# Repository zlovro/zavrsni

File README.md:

## O projektu

Završni rad za kraj školovanja u srednjoj školi (Tehničkoj školi Daruvar).

## Što je ovo?
## Ideja i motivacija
## Odabir sklopova
## Hardverska izvedba
## Elektronički dizajn
## Elektronička shema
## Softverska izvedba
## Primjer rada
## Troškovi izvedbe projekta

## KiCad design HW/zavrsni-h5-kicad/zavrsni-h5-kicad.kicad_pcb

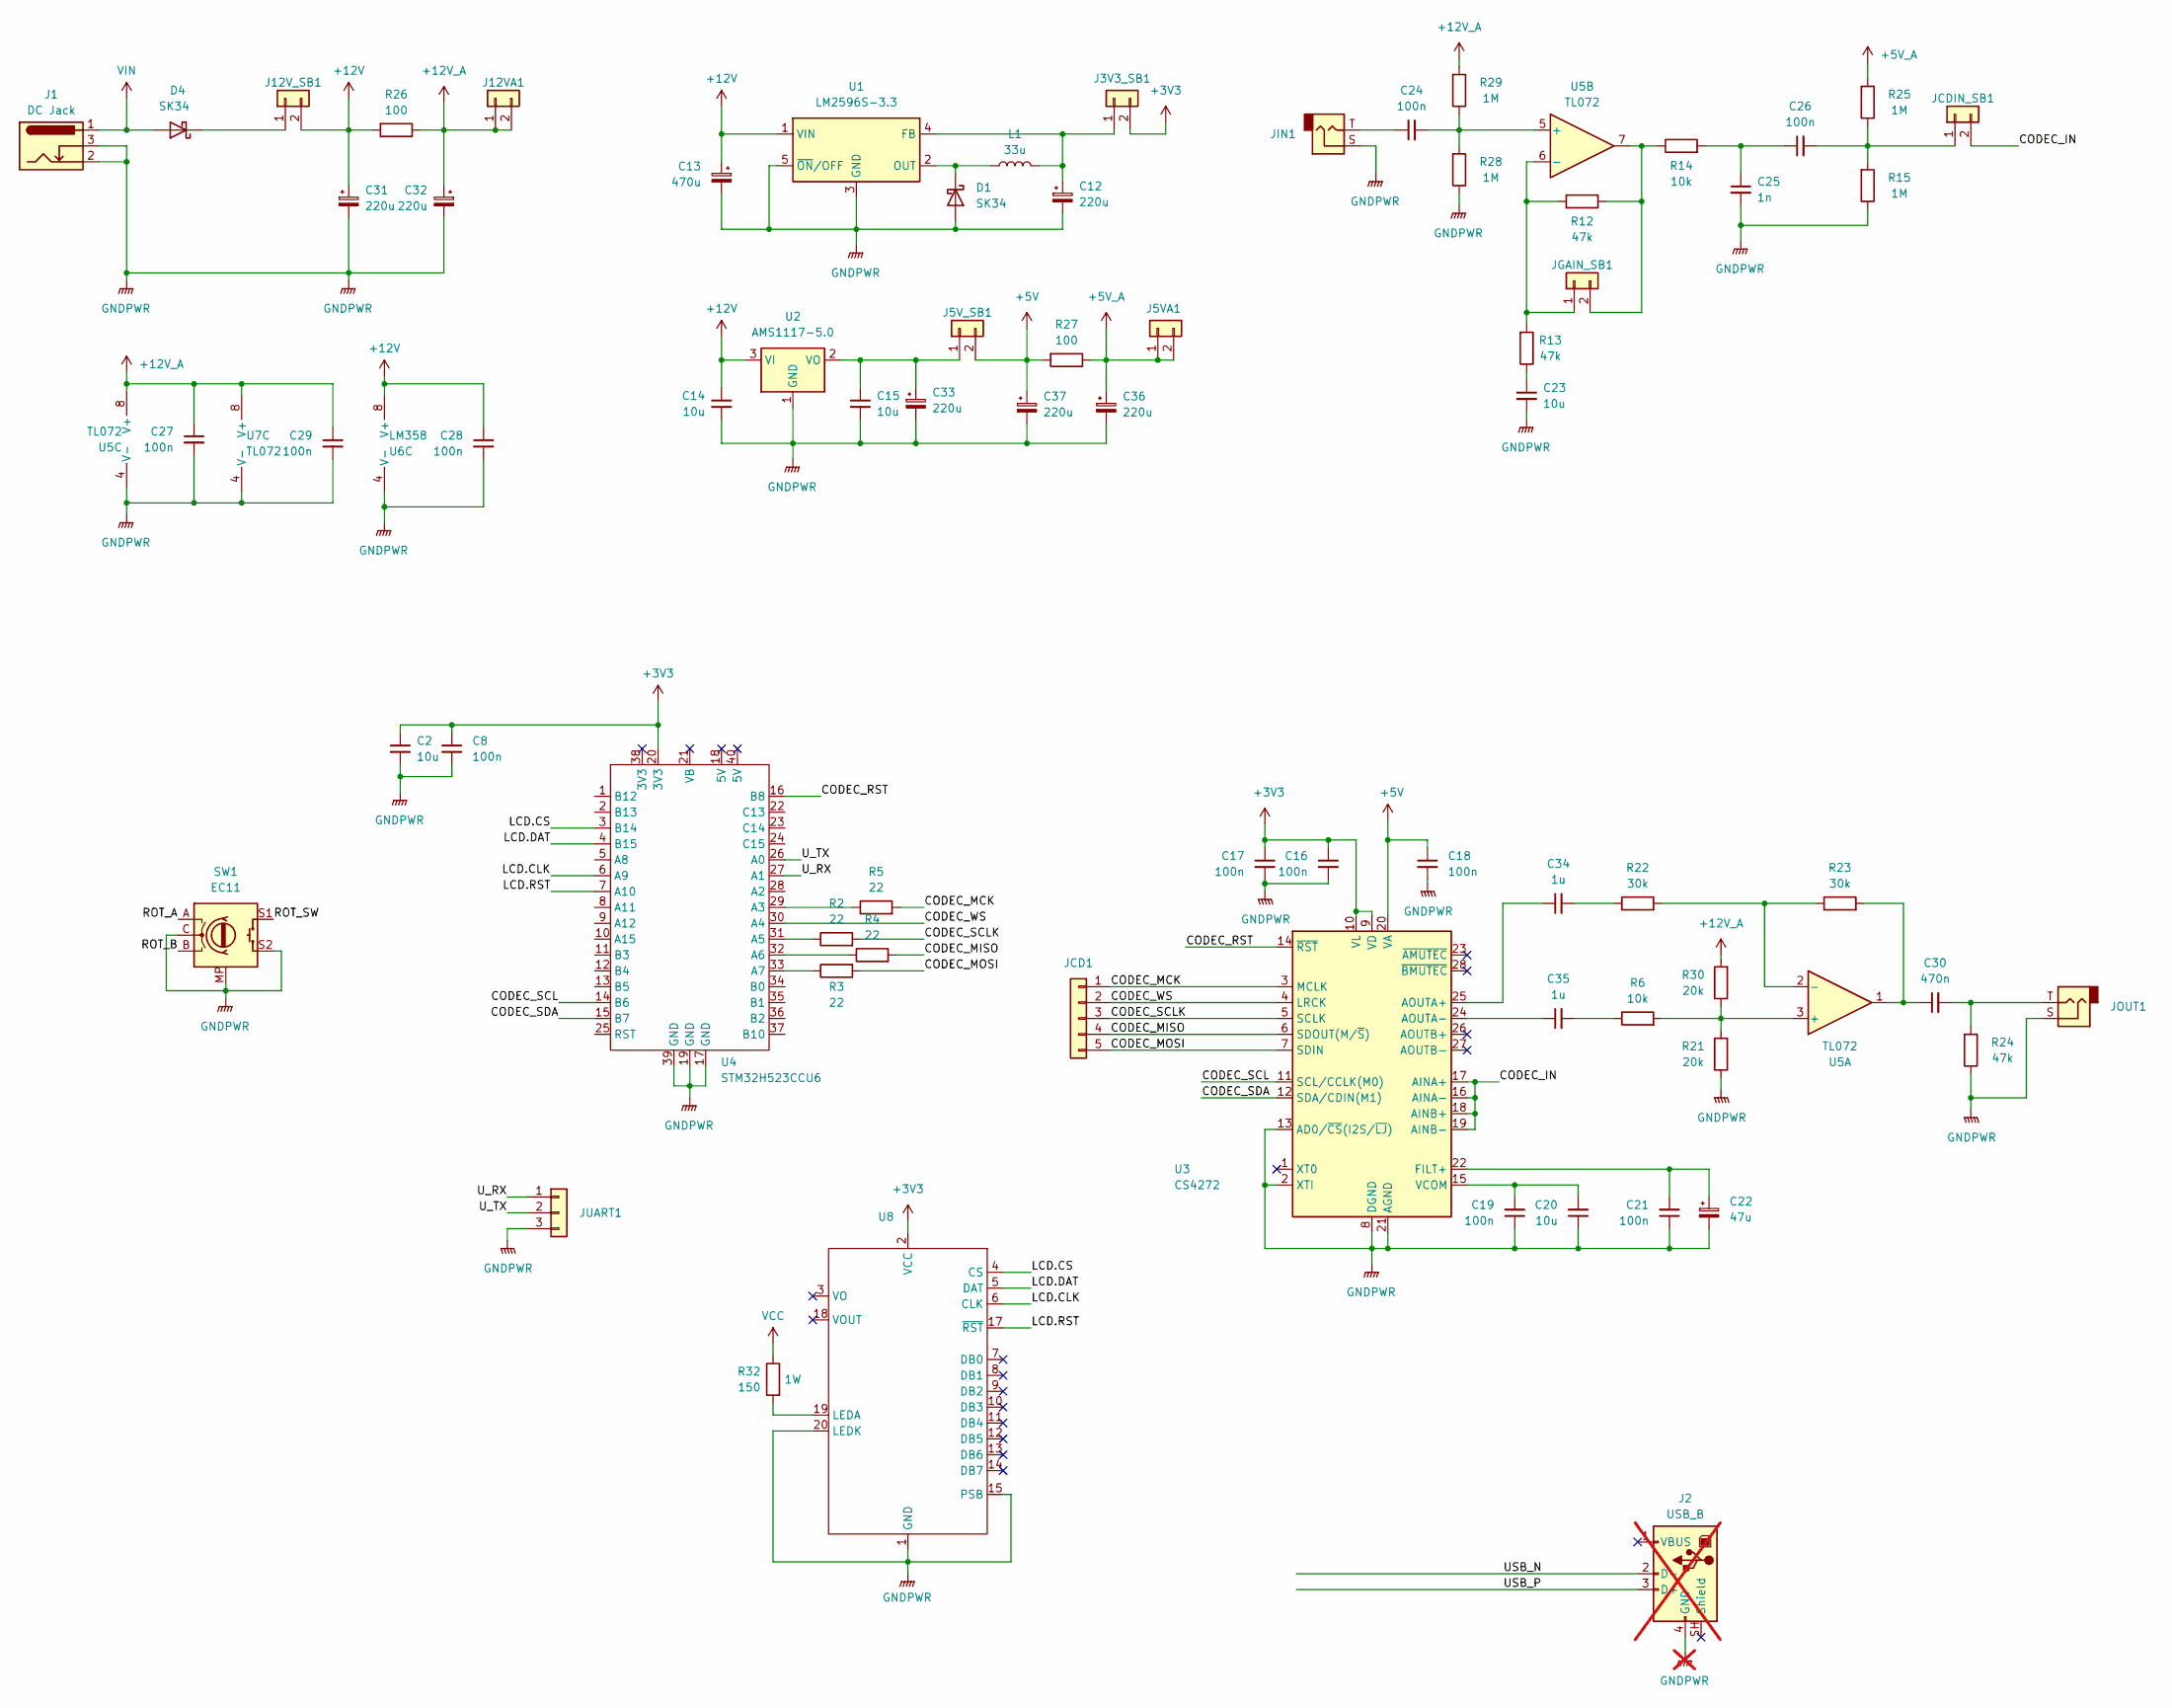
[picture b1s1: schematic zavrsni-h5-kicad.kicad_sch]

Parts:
C2, C14, C15, C20, C23: 10u; C_1206_3216Metric_Pad1.33x1.80mm_HandSolder
C8, C16, C17, C18, C19, C21, C24, C26, C27, C28, C29: 100n; C_1206_3216Metric_Pad1.33x1.80mm_HandSolder
C12, C31, C32, C33, C36, C37: 220u; CP_Radial_D5.0mm_P2.00mm
C13: 470u; CP_Radial_D8.0mm_P3.50mm
C22: 47u; CP_Radial_D4.0mm_P1.50mm
C25: 1n; C_1206_3216Metric_Pad1.33x1.80mm_HandSolder
C30: 470n; C_1206_3216Metric_Pad1.33x1.80mm_HandSolder
C34, C35: 1u; C_1206_3216Metric_Pad1.33x1.80mm_HandSolder
D1, D4: SK34; D_SMB_Handsoldering
J1: DC Jack; BarrelJack_Horizontal
J2: USB_B; USB_B_OST_USB-B1HSxx_Horizontal; not fitted
J3V3_SB1, J5VA1, J5V_SB1, J12VA1, J12V_SB1: Conn_01x02; PinHeader_1x02_P2.54mm_Vertical
JCD1: Conn_01x05; PinHeader_1x05_P2.54mm_Vertical
JCDIN_SB1: Conn_01x02; PinHeader_1x02_P2.54mm_Vertical
JGAIN_SB1: Conn_01x02; SolderJumper-2_P1.3mm_Open_TrianglePad1.0x1.5mm
JIN1: AudioJack2; 6.35 horizontalni 4pin samesky TS NC
JOUT1: AudioJack2; 6.35 horizontalni 4pin samesky TS NC
JUART1: Conn_01x03; PinHeader_1x03_P2.54mm_Vertical
L1: 33u; L_Coilcraft_MSS1038-XXX
R2, R3, R4, R5: 22; R_1206_3216Metric_Pad1.30x1.75mm_HandSolder
R6, R14: 10k; R_1206_3216Metric_Pad1.30x1.75mm_HandSolder
R12, R13, R24: 47k; R_1206_3216Metric_Pad1.30x1.75mm_HandSolder
R15, R25, R28, R29: 1M; R_1206_3216Metric_Pad1.30x1.75mm_HandSolder
R21, R30: 20k; R_1206_3216Metric_Pad1.30x1.75mm_HandSolder
R22, R23: 30k; R_1206_3216Metric_Pad1.30x1.75mm_HandSolder
R26, R27: 100; R_1206_3216Metric_Pad1.30x1.75mm_HandSolder
R32: 150; R_Axial_DIN0411_L9.9mm_D3.6mm_P12.70mm_Horizontal
SW1: EC11; ec11
U1: LM2596S-3.3; TO-263-5_TabPin3
U2: AMS1117-5.0; SOT-223-3_TabPin2
U3: CS4272; TSSOP28 adapter
U4: STM32H523CCU6; STM32H523CCU6-WeAct
U5, U7: TL072; DIP-8_W7.62mm_LongPads
U6: LM358; DIP-8_W7.62mm_LongPads
U8: LCD_12864-21M_V1.5

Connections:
+3V3: C2.1, C8.1, C16.1, C17.1, J3V3_SB1.2, U3.9 (VD), U3.10 (VL), U4.20 (3V3), U8.2 (VCC)
+5V: C18.1, C37.1, J5V_SB1.2, R27.2, U3.20 (VA)
+5V_A: C36.1, J5VA1.1, J5VA1.2, R25.2, R27.1
+12V: C13.1, C14.1, C28.1, C31.1, J12V_SB1.2, R26.2, U1.1 (VIN), U2.3 (VI), U6.8 (V+)
+12V_A: C27.1, C29.1, C32.1, J12VA1.1, J12VA1.2, R26.1, R29.2, R30.2, U5.8 (V+), U7.8 (V+)
/CODEC_IN: JCDIN_SB1.2, U3.16 (AINA-), U3.17 (AINA+), U3.18 (AINB+), U3.19 (AINB-)
/CODEC_MCK: JCD1.1, R5.2, U3.3 (MCLK)
/CODEC_MISO: JCD1.4, R4.2, U3.6 (SDOUT(M/~S))
/CODEC_MOSI: JCD1.5, R3.2, U3.7 (SDIN)
/CODEC_RST: U3.14 (~RST), U4.16 (B8)
/CODEC_SCL: U3.11 (SCL/CCLK(M0)), U4.14 (B6)
/CODEC_SCLK: JCD1.3, R2.2, U3.5 (SCLK)
/CODEC_SDA: U3.12 (SDA/CDIN(M1)), U4.15 (B7)
/CODEC_WS: JCD1.2, U3.4 (LRCK), U4.30 (A4)
/LCD.CLK: U4.6 (A9), U8.6 (CLK)
/LCD.CS: U4.3 (B14), U8.4 (CS)
/LCD.DAT: U4.4 (B15), U8.5 (DAT)
/LCD.RST: U4.7 (A10), U8.17 (~RST)
/ROT_A: SW1.A
/ROT_B: SW1.B
/ROT_SW: SW1.S1
/USB_N: J2.2 (D-)
/USB_P: J2.3 (D+)
/U_RX: JUART1.1, U4.27 (A1)
/U_TX: JUART1.2, U4.26 (A0)
GNDPWR: C2.2, C8.2, C12.2, C13.2, C14.2, C15.2, C16.2, C17.2, C18.2, C19.1, C20.1, C21.1, C22.2, C23.2, C25.2, C27.2, C28.2, C29.2, C31.2, C32.2, C33.2, C36.2, C37.2, D1.2 (A), J1.2, J1.3, J2.4 (GND), JIN1.S, JOUT1.S, JUART1.3, R15.1, R21.1, R24.1, R28.1, SW1.C, SW1.MP, SW1.S2, U1.3 (GND), U1.5 (~ON/OFF), U2.1 (GND), U3.2 (XTI), U3.8 (DGND), U3.13 (AD0/~CS(I2S/~LJ)), U3.21 (AGND), U4.17 (GND), U4.19 (GND), U4.39 (GND), U5.4 (V-), U6.4 (V-), U7.4 (V-), U8.1 (GND), U8.15 (PSB), U8.20 (LEDK)
unnamed: C23.1, R13.1
unnamed: C24.1, JIN1.T
unnamed: C25.1, C26.1, R14.2
unnamed: C30.1, R23.2, U5.1
unnamed: C30.2, JOUT1.T, R24.2
unnamed: C34.2, R22.1
unnamed: C35.2, R6.1
unnamed: D1.1 (K), L1.1, U1.2 (OUT)
unnamed: D4.1 (K), J12V_SB1.1
unnamed: C12.1, J3V3_SB1.1, L1.2, U1.4 (FB)
unnamed: C15.1, C33.1, J5V_SB1.1, U2.2 (VO)
unnamed: C26.2, JCDIN_SB1.1, R15.2, R25.1
unnamed: JGAIN_SB1.1, R12.2, R13.2, U5.6 (-)
unnamed: JGAIN_SB1.2, R12.1, R14.1, U5.7
unnamed: C34.1, U3.25 (AOUTA+)
unnamed: C35.1, U3.24 (AOUTA-)
unnamed: C21.2, C22.1, U3.22 (FILT+)
unnamed: C19.2, C20.2, U3.15 (VCOM)
unnamed: R5.1, U4.29 (A3)
unnamed: R2.1, U4.31 (A5)
unnamed: R4.1, U4.32 (A6)
unnamed: R3.1, U4.33 (A7)
unnamed: R6.2, R21.2, R30.1, U5.3 (+)
unnamed: R22.2, R23.1, U5.2 (-)
unnamed: C24.2, R28.2, R29.1, U5.5 (+)
unnamed: R32.2, U8.19 (LEDA)
VCC: R32.1
VIN: D4.2 (A), J1.1

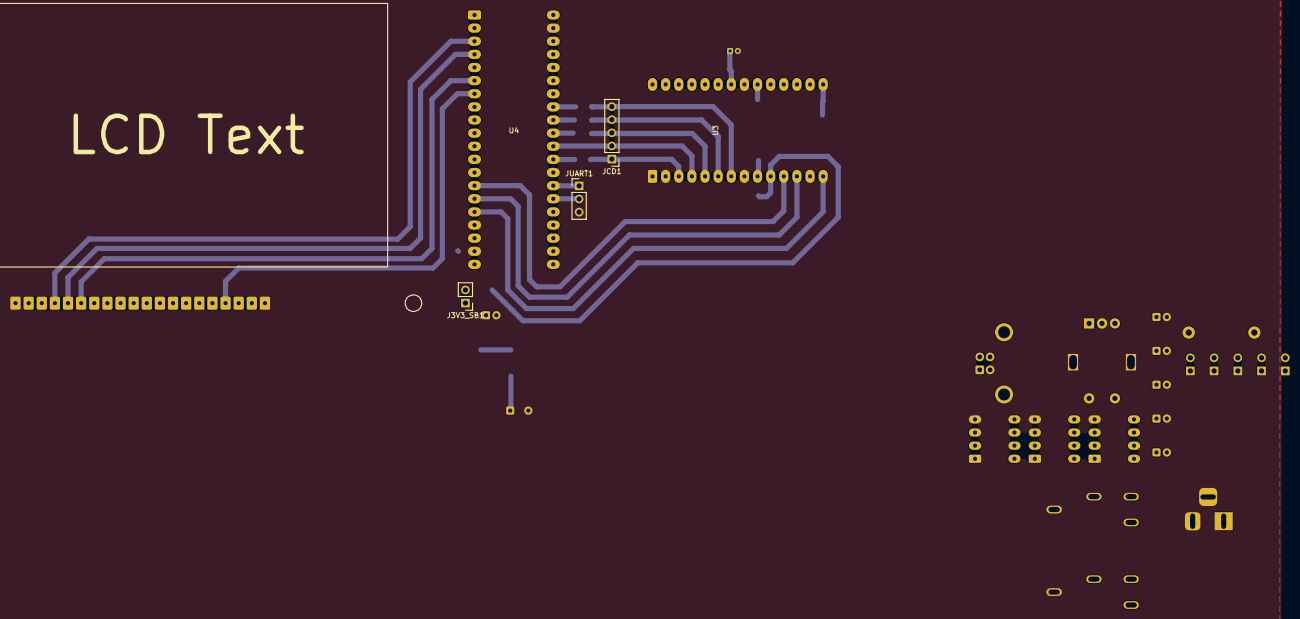
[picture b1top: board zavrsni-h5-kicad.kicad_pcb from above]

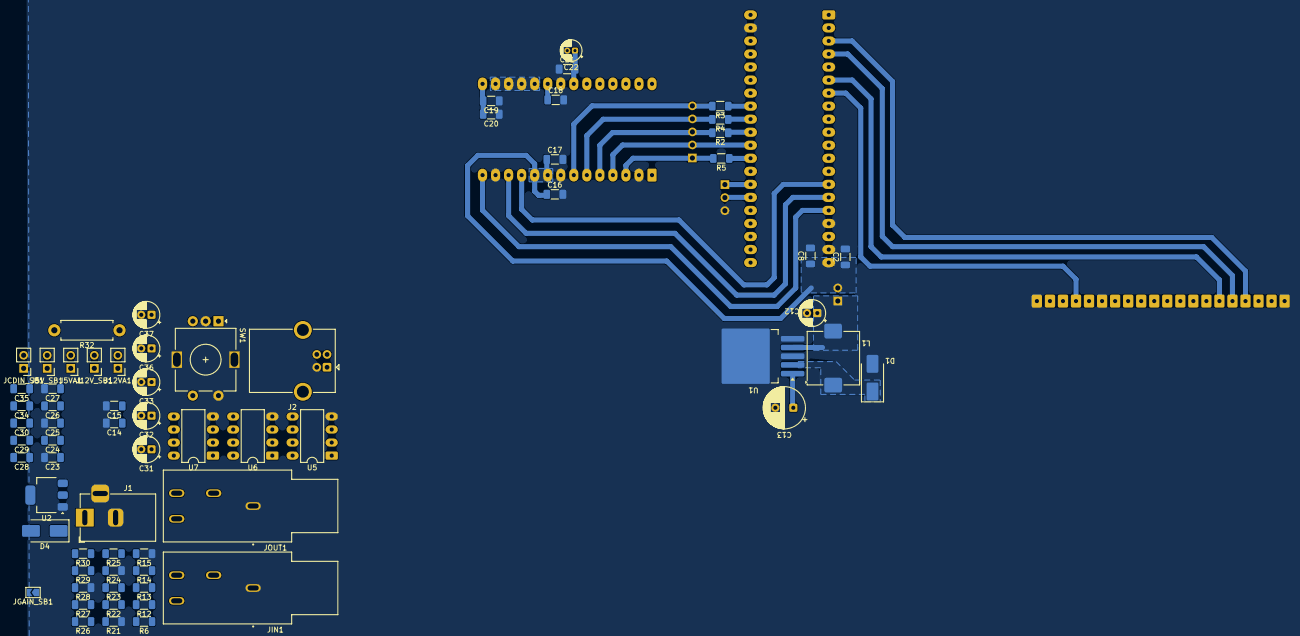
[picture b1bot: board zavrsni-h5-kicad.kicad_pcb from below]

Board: 2 copper layers, 73 parts (67 on the bottom side), 48 nets.

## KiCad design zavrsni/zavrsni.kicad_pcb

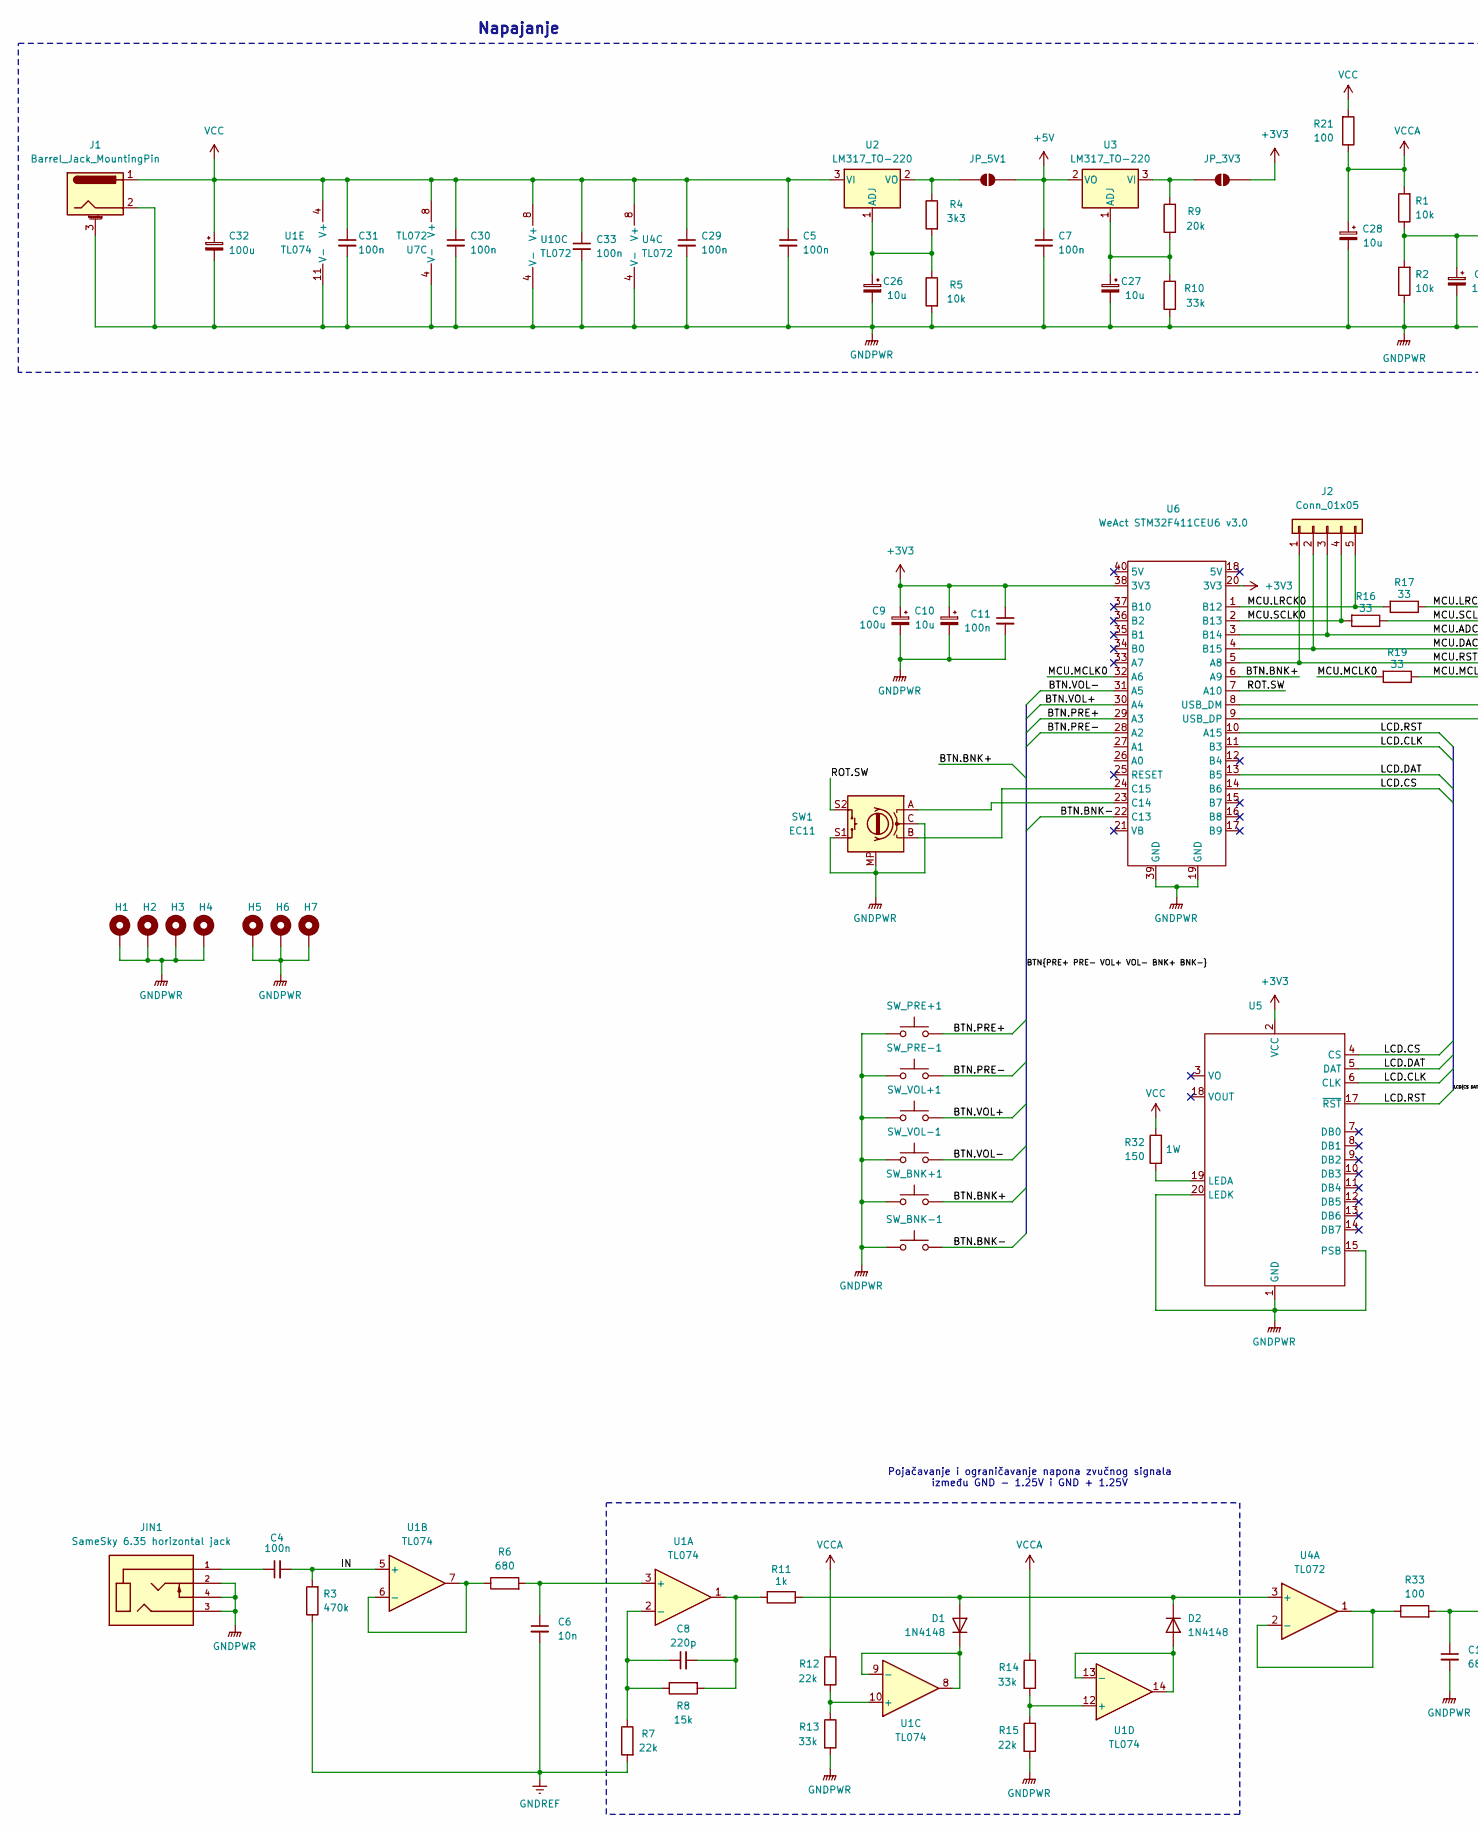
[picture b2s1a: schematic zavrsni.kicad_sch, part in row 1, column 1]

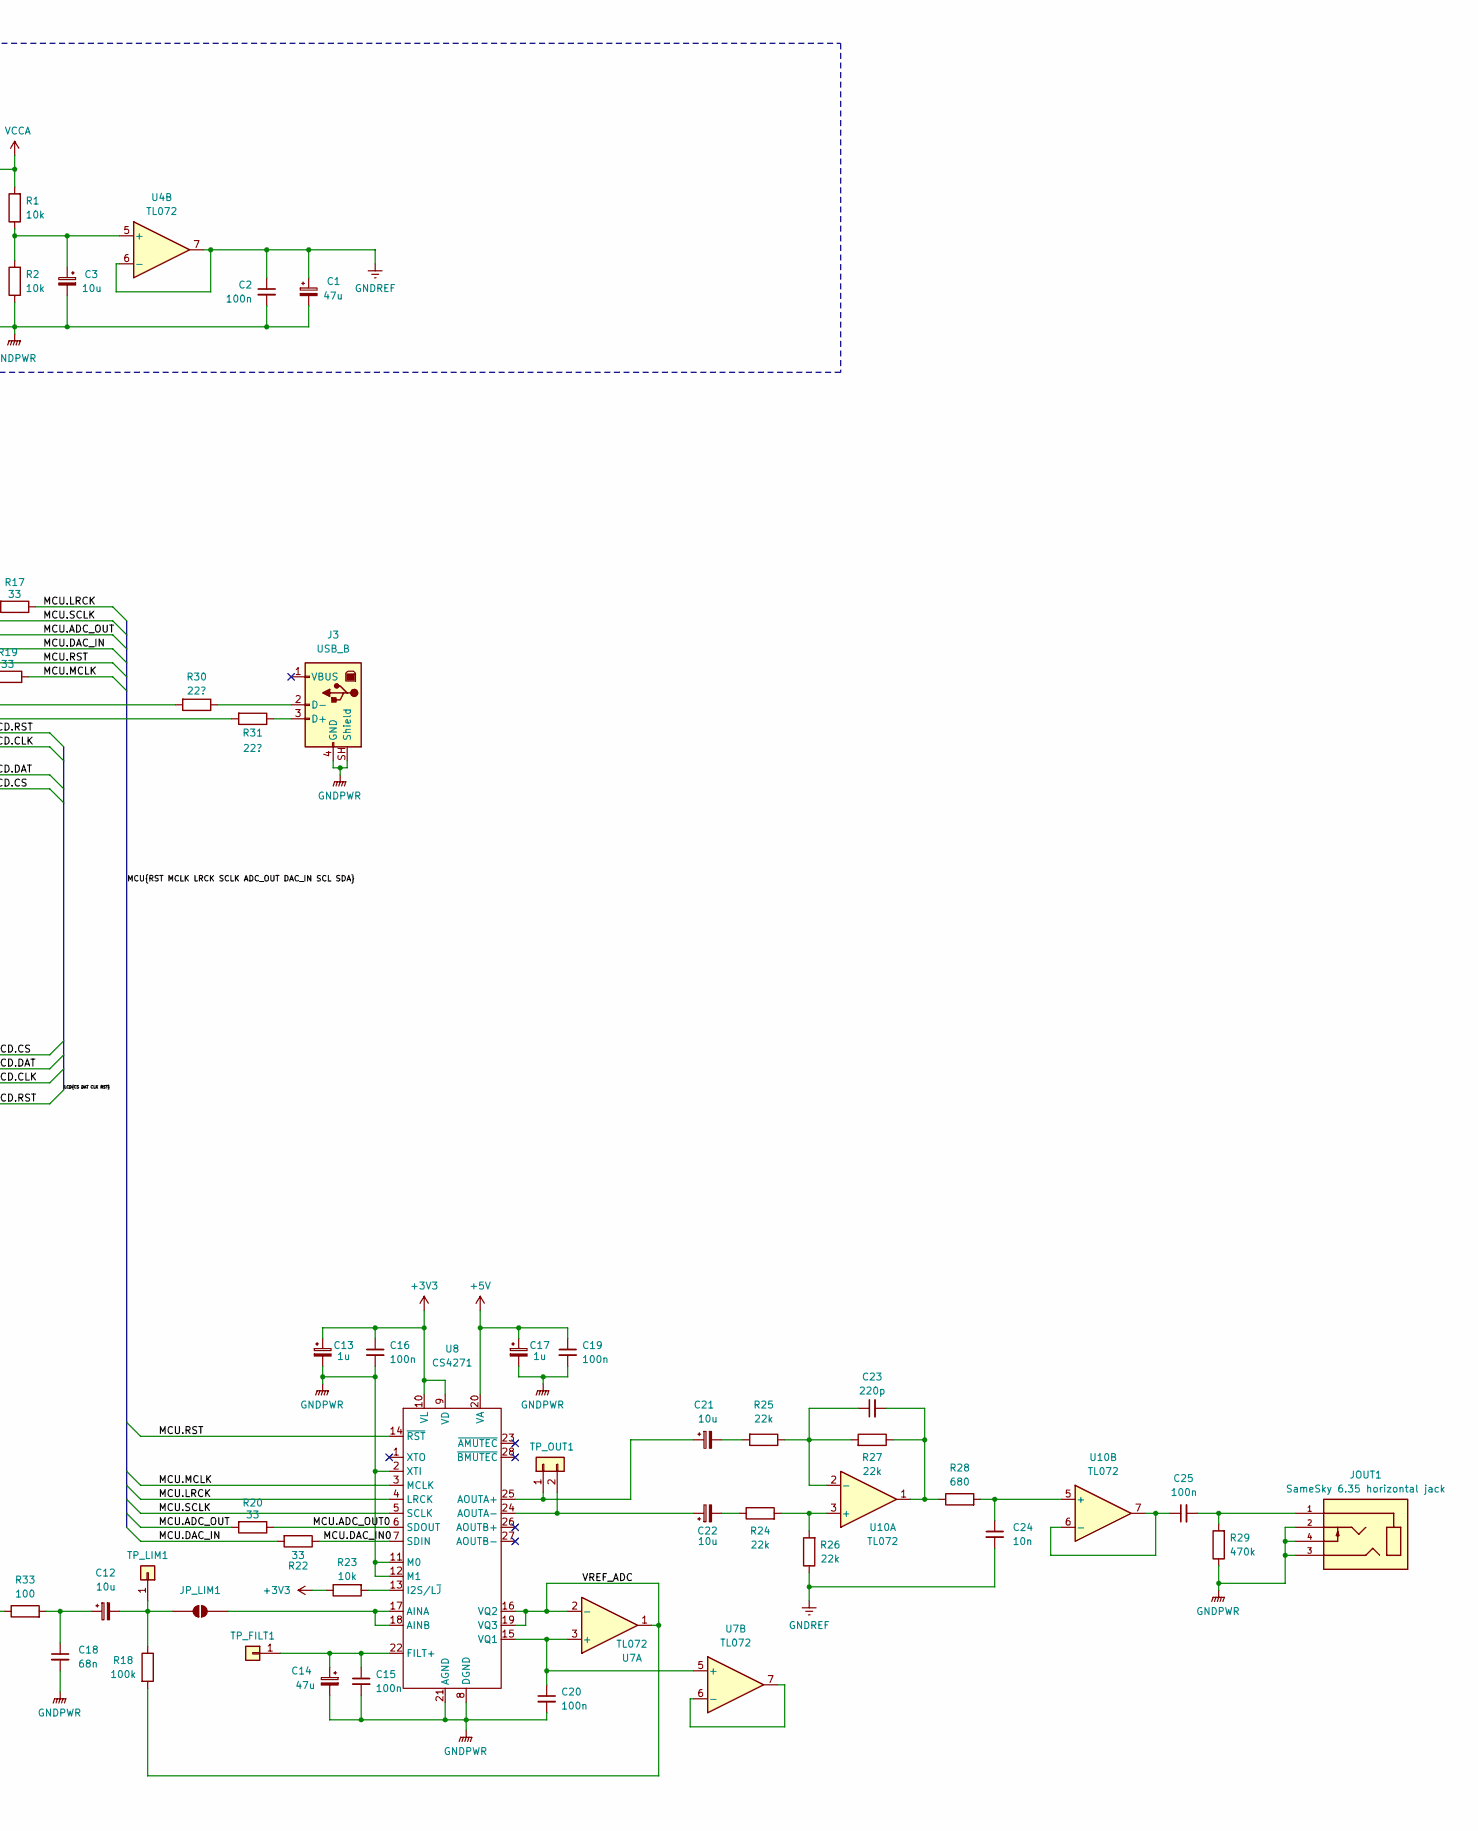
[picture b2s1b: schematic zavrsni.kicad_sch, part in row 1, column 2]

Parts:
C1, C14: 47u; CP_Radial_D5.0mm_P2.50mm
C2, C4, C5, C7, C11, C15, C16, C19, C20, C25, C30, C31, C33: 100n; C_Disc_D5.0mm_W2.5mm_P5.00mm
C3, C10, C12, C21, C22, C26, C27, C28: 10u; CP_Radial_D5.0mm_P2.50mm
C6, C24: 10n; C_Disc_D5.0mm_W2.5mm_P2.50mm
C8, C23: 220p; C_Disc_D5.0mm_W2.5mm_P2.50mm
C9, C32: 100u; CP_Radial_D5.0mm_P2.50mm
C13, C17: 1u; CP_Radial_D5.0mm_P2.50mm
C18: 68n; C_Disc_D5.0mm_W2.5mm_P2.50mm
C29: 100n; C_Disc_D5.0mm_W2.5mm_P2.50mm
D1, D2: 1N4148; D_DO-35_SOD27_P2.54mm_Vertical_AnodeUp
H1, H2, H3, H4, H5, H6, H7: MountingHole_Pad; MountingHole_2.1mm
J1: Barrel_Jack_MountingPin; BarrelJack_Horizontal
J2: Conn_01x05; PinHeader_1x05_P2.54mm_Vertical
J3: USB_B; USB B Female
JIN1: SameSky 6.35 horizontal jack; 6.35 horizontalni 4pin samesky; PARTREV 1.0
JOUT1: SameSky 6.35 horizontal jack; 6.35 horizontalni 4pin samesky; PARTREV 1.0
JP_3V3, JP_5V1: SolderJumper_2_Open; SolderJumper-2_P1.3mm_Open_RoundedPad1.0x1.5mm
JP_LIM1: SolderJumper_2_Open; SolderJumper-2_P1.3mm_Open_RoundedPad1.0x1.5mm
R1: 10k; R_Axial_DIN0207_L6.3mm_D2.5mm_P15.24mm_Horizontal
R2, R5, R23: 10k; R_Axial_DIN0207_L6.3mm_D2.5mm_P2.54mm_Vertical
R3, R29: 470k; R_Axial_DIN0207_L6.3mm_D2.5mm_P2.54mm_Vertical
R4: 3k3; R_Axial_DIN0207_L6.3mm_D2.5mm_P2.54mm_Vertical
R6: 680; R_Axial_DIN0207_L6.3mm_D2.5mm_P7.62mm_Horizontal
R7, R12, R15, R24, R25, R27: 22k; R_Axial_DIN0207_L6.3mm_D2.5mm_P2.54mm_Vertical
R8: 15k; R_Axial_DIN0207_L6.3mm_D2.5mm_P2.54mm_Vertical
R9: 20k; R_Axial_DIN0207_L6.3mm_D2.5mm_P2.54mm_Vertical
R10: 33k; R_Axial_DIN0207_L6.3mm_D2.5mm_P5.08mm_Vertical
R11: 1k; R_Axial_DIN0207_L6.3mm_D2.5mm_P5.08mm_Vertical
R13, R14: 33k; R_Axial_DIN0207_L6.3mm_D2.5mm_P2.54mm_Vertical
R16, R17, R20, R22: 33; R_Axial_DIN0207_L6.3mm_D2.5mm_P2.54mm_Vertical
R18: 100k; R_Axial_DIN0207_L6.3mm_D2.5mm_P10.16mm_Horizontal
R19: 33; R_Axial_DIN0207_L6.3mm_D2.5mm_P15.24mm_Horizontal
R21: 100; R_Axial_DIN0207_L6.3mm_D2.5mm_P7.62mm_Horizontal
R26: 22k; R_Axial_DIN0207_L6.3mm_D2.5mm_P5.08mm_Vertical
R28: 680; R_Axial_DIN0207_L6.3mm_D2.5mm_P2.54mm_Vertical
R30: 22?; R_Axial_DIN0207_L6.3mm_D2.5mm_P15.24mm_Horizontal
R31: 22?; R_Axial_DIN0207_L6.3mm_D2.5mm_P7.62mm_Horizontal
R32: 150; R_Axial_DIN0411_L9.9mm_D3.6mm_P12.70mm_Horizontal
R33: 100; R_Axial_DIN0207_L6.3mm_D2.5mm_P2.54mm_Vertical
SW1: EC11; ec11
SW_BNK+1: SW_Push; SW_PUSH_6mm_H13mm
SW_BNK-1: SW_Push; SW_PUSH_6mm_H13mm
SW_PRE+1: SW_Push; SW_PUSH_6mm_H13mm
SW_PRE-1: SW_Push; SW_PUSH_6mm_H13mm
SW_VOL+1: SW_Push; SW_PUSH_6mm_H13mm
SW_VOL-1: SW_Push; SW_PUSH_6mm_H13mm
TP_FILT1: Conn_01x01; PinHeader_1x01_P2.54mm_Vertical
TP_LIM1: Conn_01x01; PinHeader_1x01_P2.54mm_Vertical
TP_OUT1: Conn_01x02; PinHeader_1x02_P2.54mm_Vertical
U1: TL074; DIP-14_W7.62mm
U2, U3: LM317_TO-220; TO-220-3_Vertical
U4, U7, U10: TL072; DIP-8_W7.62mm
U5: LCD_12864-21M_V1.5
U6: WeAct STM32F411CEU6 v3.0; STM32F411CEU6 WeAct V3.0
U8: CS4271; TSSOP-28_4.4x9.7mm_P0.65mm

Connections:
+3V3: C9.1, C10.1, C11.1, C13.1, C16.1, JP_3V3.2 (B), R23.1, U5.2 (VCC), U6.20 (3V3), U6.38 (3V3), U8.9 (VD), U8.10 (VL)
+5V: C7.1, C17.1, C19.1, JP_5V1.2 (B), U3.2 (VO), U8.20 (VA)
/BTN.BNK+: SW_BNK+1.2, U6.6 (A9)
/BTN.BNK-: SW_BNK-1.2, U6.22 (C13)
/BTN.PRE+: SW_PRE+1.2, U6.29 (A3)
/BTN.PRE-: SW_PRE-1.2, U6.28 (A2)
/BTN.VOL+: SW_VOL+1.2, U6.30 (A4)
/BTN.VOL-: SW_VOL-1.2, U6.31 (A5)
/IN: C4.2, R3.2, U1.5 (+)
/LCD.CLK: U5.6 (CLK), U6.11 (B3)
/LCD.CS: U5.4 (CS), U6.14 (B6)
/LCD.DAT: U5.5 (DAT), U6.13 (B5)
/LCD.RST: U5.17 (~RST), U6.10 (A15)
/MCU.ADC_OUT: J2.3, R20.2, U6.3 (B14)
/MCU.ADC_OUT0: R20.1, U8.6 (SDOUT)
/MCU.DAC_IN: J2.2, R22.2, U6.4 (B15)
/MCU.DAC_IN0: R22.1, U8.7 (SDIN)
/MCU.LRCK: R17.1, U8.4 (LRCK)
/MCU.LRCK0: J2.5, R17.2, U6.1 (B12)
/MCU.MCLK: R19.1, U8.3 (MCLK)
/MCU.MCLK0: R19.2, U6.32 (A6)
/MCU.RST: J2.1, U6.5 (A8), U8.14 (~RST)
/MCU.SCLK: R16.1, U8.5 (SCLK)
/MCU.SCLK0: J2.4, R16.2, U6.2 (B13)
/ROT.SW: SW1.S2, U6.7 (A10)
/VREF_ADC: R18.2, U7.1, U7.2 (-), U8.16 (VQ2), U8.19 (VQ3)
GNDPWR: C1.2, C2.2, C3.2, C5.2, C7.2, C9.2, C10.2, C11.2, C13.2, C14.2, C15.2, C16.2, C17.2, C18.2, C19.2, C20.2, C26.2, C27.2, C28.2, C29.2, C30.2, C31.2, C32.2, C33.2, H1.1, H2.1, H3.1, H4.1, H5.1, H6.1, H7.1, J1.2, J1.3 (MountPin_3), J3.4 (GND), J3.SH (Shield), JIN1.2, JIN1.3, JIN1.4, JOUT1.2, JOUT1.3, JOUT1.4, R2.1, R5.2, R10.2, R13.2, R15.2, R29.1, SW1.C, SW1.MP, SW1.S1, SW_BNK+1.1, SW_BNK-1.1, SW_PRE+1.1, SW_PRE-1.1, SW_VOL+1.1, SW_VOL-1.1, U1.11 (V-), U4.4 (V-), U5.1 (GND), U5.15 (PSB), U5.20 (LEDK), U6.19 (GND), U6.39 (GND), U7.4 (V-), U8.2 (XTI), U8.8 (DGND), U8.11 (M0), U8.12 (M1), U8.21 (AGND), U10.4 (V-)
GNDREF: C1.1, C2.1, C6.2, C24.2, R3.1, R7.2, R26.1, U4.6 (-), U4.7
unnamed: C4.1, JIN1.1
unnamed: C8.2, R8.2, R11.2, U1.1
unnamed: C12.1, C18.1, R33.2
unnamed: C21.2, R25.2
unnamed: C22.2, R24.1
unnamed: C23.2, R27.1, R28.1, U10.1
unnamed: C25.2, JOUT1.1, R29.2
unnamed: D1.2 (A), D2.1 (K), R11.1, U4.3 (+)
unnamed: D1.1 (K), U1.8, U1.9 (-)
unnamed: D2.2 (A), U1.13 (-), U1.14
unnamed: J3.3 (D+), R31.1
unnamed: J3.2 (D-), R30.1
unnamed: JP_3V3.1 (A), R9.1, U3.3 (VI)
unnamed: JP_5V1.1 (A), R4.1, U2.2 (VO)
unnamed: C12.2, JP_LIM1.1 (A), R18.1, TP_LIM1.1 (Pin_1_1)
unnamed: JP_LIM1.2 (B), U8.17 (AINA), U8.18 (AINB)
unnamed: C14.1, C15.1, TP_FILT1.1 (Pin_1_1), U8.22 (FILT+)
unnamed: C21.1, TP_OUT1.1, U8.25 (AOUTA+)
unnamed: C22.1, TP_OUT1.2, U8.24 (AOUTA-)
unnamed: C6.1, R6.2, U1.3 (+)
unnamed: C8.1, R7.1, R8.1, U1.2 (-)
unnamed: R6.1, U1.6 (-), U1.7
unnamed: R12.2, R13.1, U1.10 (+)
unnamed: R14.2, R15.1, U1.12 (+)
unnamed: C26.1, R4.2, R5.1, U2.1 (ADJ)
unnamed: C27.1, R9.2, R10.1, U3.1 (ADJ)
unnamed: R33.1, U4.1, U4.2 (-)
unnamed: C3.1, R1.1, R2.2, U4.5 (+)
unnamed: R32.2, U5.19 (LEDA)
unnamed: SW1.A, U6.23 (C14)
unnamed: SW1.B, U6.24 (C15)
unnamed: R30.2, U6.8 (USB_DM)
unnamed: R31.2, U6.9 (USB_DP)
unnamed: C20.1, U7.3 (+), U7.5 (+), U8.15 (VQ1)
unnamed: U7.6 (-), U7.7
unnamed: R23.2, U8.13 (I2S/L~J)
unnamed: R24.2, R26.2, U10.3 (+)
unnamed: C23.1, R25.1, R27.2, U10.2 (-)
unnamed: C24.1, R28.2, U10.5 (+)
unnamed: C25.1, U10.6 (-), U10.7
VCC: C5.1, C29.1, C30.1, C31.1, C32.1, C33.1, J1.1, R21.2, R32.1, U1.4 (V+), U2.3 (VI), U4.8 (V+), U7.8 (V+), U10.8 (V+)
VCCA: C28.1, R1.2, R12.1, R14.1, R21.1

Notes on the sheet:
Napajanje
Pojačavanje i ograničavanje napona zvučnog signala između GND - 1.25V i GND + 1.25V

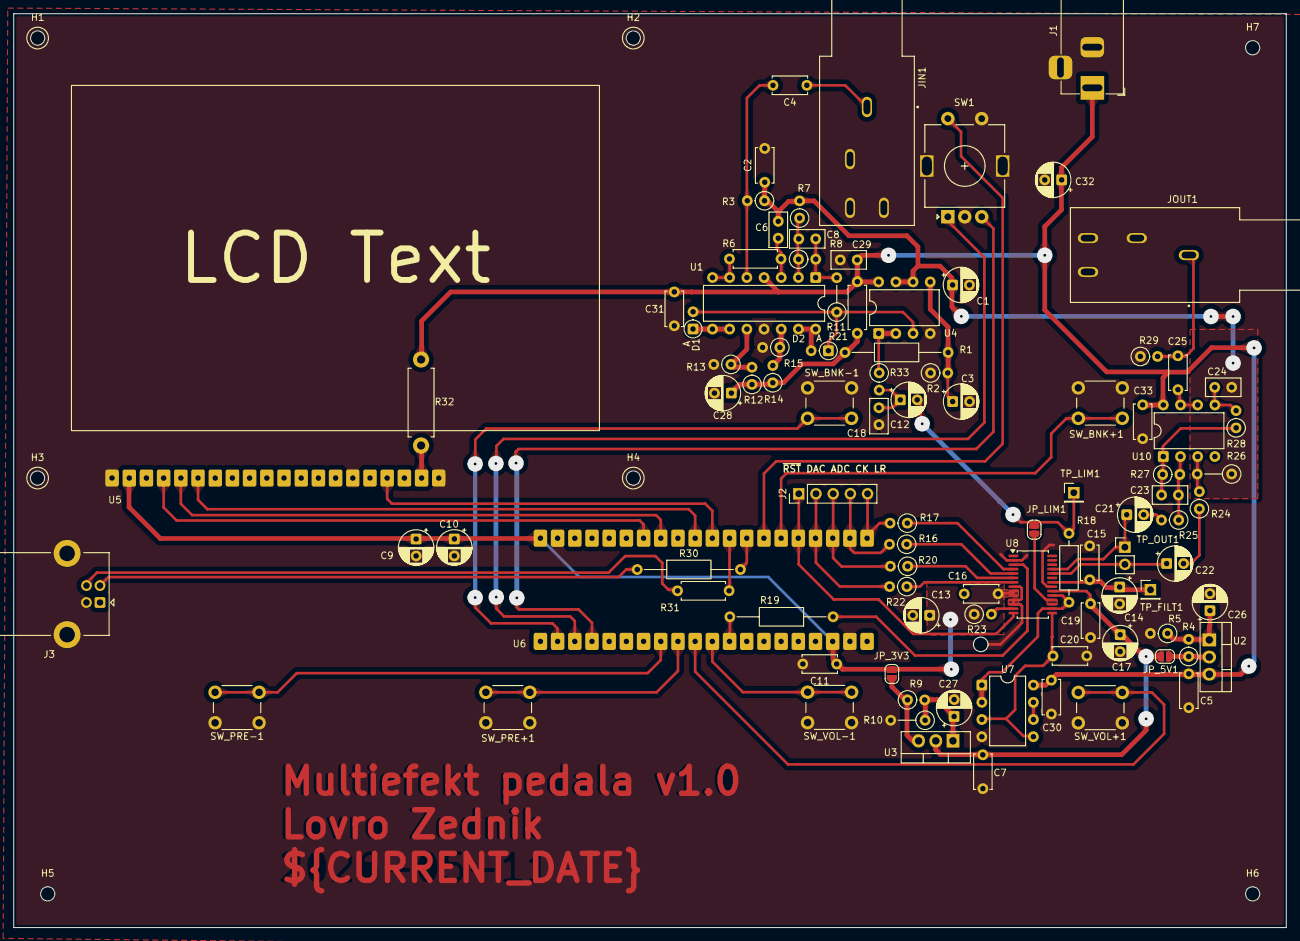
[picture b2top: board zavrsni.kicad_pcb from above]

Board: 2 copper layers, 188.0 x 135.0 mm, 102 parts (0 on the bottom side), 70 nets.

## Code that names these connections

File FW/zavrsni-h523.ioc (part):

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Mcu.Name=STM32H523CCUx
Mcu.Package=UFQFPN48
Mcu.UserName=STM32H523CCUx
PA0.GPIOParameters=GPIO_Label
PA0.GPIO_Label=U_TX
PA0.Mode=Asynchronous
PA0.Signal=UART4_TX
PA1.GPIOParameters=GPIO_Label
PA1.GPIO_Label=U_RX
PA1.Mode=Asynchronous
PA1.Signal=UART4_RX
PA10.GPIOParameters=GPIO_Label
PA10.GPIO_Label=LCD_RST
PA10.Signal=GPIO_Output
PA13(JTMS/SWDIO).Mode=Serial_Wire
PA13(JTMS/SWDIO).Signal=DEBUG_JTMS-SWDIO
PA14(JTCK/SWCLK).Mode=Serial_Wire
PA14(JTCK/SWCLK).Signal=DEBUG_JTCK-SWCLK
PA3.GPIOParameters=GPIO_Label
PA3.GPIO_Label=CODEC_MCK
PA3.Signal=S_TIM15_CH2
PA4.GPIOParameters=GPIO_Label
PA4.GPIO_Label=CODEC_LRCK
PA4.Mode=Full_Duplex_Master
PA4.Signal=I2S1_WS
PA5.GPIOParameters=GPIO_Label
PA5.GPIO_Label=CODEC_SCK
PA5.Mode=Full_Duplex_Master
PA5.Signal=I2S1_CK
PA6.GPIOParameters=GPIO_Label
PA6.GPIO_Label=CODEC_MISO
PA6.Mode=Full_Duplex_Master
PA6.Signal=I2S1_SDI
PA7.GPIOParameters=GPIO_Label
PA7.GPIO_Label=CODEC_MOSI
PA7.Mode=Full_Duplex_Master
PA7.Signal=I2S1_SDO
PA9.GPIOParameters=GPIO_Label
PA9.GPIO_Label=LCD_CLK
PA9.Mode=TX_Only_Simplex_Unidirect_Master
PA9.Signal=SPI2_SCK
PB14.GPIOParameters=GPIO_Label
PB14.GPIO_Label=LCD_CS
PB14.Signal=GPIO_Output
PB15.GPIOParameters=GPIO_Label
PB15.GPIO_Label=LCD_DAT
PB15.Mode=TX_Only_Simplex_Unidirect_Master
PB15.Signal=SPI2_MOSI
PB6.GPIOParameters=GPIO_Label
PB6.GPIO_Label=CODEC_SCL
PB6.Mode=I2C
PB6.Signal=I2C1_SCL
PB7.GPIOParameters=GPIO_Label
PB7.GPIO_Label=CODEC_SDA
PB7.Mode=I2C
PB7.Signal=I2C1_SDA
PB8.GPIOParameters=GPIO_Label
PB8.GPIO_Label=CODEC_RST
PB8.Signal=GPIO_Output
PH0-OSC_IN(PH0).Mode=HSE-External-Oscillator
PH0-OSC_IN(PH0).Signal=RCC_OSC_IN
PH1-OSC_OUT(PH1).Mode=HSE-External-Oscillator
PH1-OSC_OUT(PH1).Signal=RCC_OSC_OUT
RCC.HSE_VALUE=8000000
RCC.SYSCLKFreq_VALUE=192000000
RCC.SYSCLKSource=RCC_SYSCLKSOURCE_PLLCLK
board=custom

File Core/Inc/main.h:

/* USER CODE BEGIN Header */
/**
  ******************************************************************************
  * @file           : main.h
  * @brief          : Header for main.c file.
  *                   This file contains the common defines of the application.
  ******************************************************************************
  * @attention
  *
  * Copyright (c) 2025 STMicroelectronics.
  * All rights reserved.
  *
  * This software is licensed under terms that can be found in the LICENSE file
  * in the root directory of this software component.
  * If no LICENSE file comes with this software, it is provided AS-IS.
  *
  ******************************************************************************
  */
/* USER CODE END Header */

/* Define to prevent recursive inclusion -------------------------------------*/
#ifndef __MAIN_H
#define __MAIN_H

#ifdef __cplusplus
extern "C" {
#endif

/* Includes ------------------------------------------------------------------*/
#include "stm32f4xx_hal.h"

/* Private includes ----------------------------------------------------------*/
/* USER CODE BEGIN Includes */

#include <impl/smallgpio.h>

/* USER CODE END Includes */

/* Exported types ------------------------------------------------------------*/
/* USER CODE BEGIN ET */

/* USER CODE END ET */

/* Exported constants --------------------------------------------------------*/
/* USER CODE BEGIN EC */

/* USER CODE END EC */

/* Exported macro ------------------------------------------------------------*/
/* USER CODE BEGIN EM */

/* USER CODE END EM */

/* Exported functions prototypes ---------------------------------------------*/
void Error_Handler(void);

/* USER CODE BEGIN EFP */

/* USER CODE END EFP */

/* Private defines -----------------------------------------------------------*/
#define ROT_B_Pin GPIO_PIN_13
#define ROT_B_GPIO_Port GPIOC
#define ROT_A_Pin GPIO_PIN_14
#define ROT_A_GPIO_Port GPIOC
#define ROT_SW_Pin GPIO_PIN_15
#define ROT_SW_GPIO_Port GPIOC
#define CODEC_MCLK_Pin GPIO_PIN_3
#define CODEC_MCLK_GPIO_Port GPIOA
#define LCD_RST_Pin GPIO_PIN_4
#define LCD_RST_GPIO_Port GPIOA
#define LCD_CLK_Pin GPIO_PIN_5
#define LCD_CLK_GPIO_Port GPIOA
#define LCD_CS_Pin GPIO_PIN_6
#define LCD_CS_GPIO_Port GPIOA
#define LCD_DAT_Pin GPIO_PIN_7
#define LCD_DAT_GPIO_Port GPIOA
#define CODEC_LRCK_Pin GPIO_PIN_12
#define CODEC_LRCK_GPIO_Port GPIOB
#define CODEC_SCLK_Pin GPIO_PIN_13
#define CODEC_SCLK_GPIO_Port GPIOB
#define CODEC_OUT_Pin GPIO_PIN_14
#define CODEC_OUT_GPIO_Port GPIOB
#define CODEC_IN_Pin GPIO_PIN_15
#define CODEC_IN_GPIO_Port GPIOB
#define CODEC_RST_Pin GPIO_PIN_8
#define CODEC_RST_GPIO_Port GPIOA
#define BTN_BNKM_Pin GPIO_PIN_4
#define BTN_BNKM_GPIO_Port GPIOB
#define BTN_BNKP_Pin GPIO_PIN_5
#define BTN_BNKP_GPIO_Port GPIOB
#define BTN_VOLM_Pin GPIO_PIN_6
#define BTN_VOLM_GPIO_Port GPIOB
#define BTN_VOLP_Pin GPIO_PIN_7
#define BTN_VOLP_GPIO_Port GPIOB
#define BTN_PREM_Pin GPIO_PIN_8
#define BTN_PREM_GPIO_Port GPIOB
#define BTN_PREP_Pin GPIO_PIN_9
#define BTN_PREP_GPIO_Port GPIOB

/* USER CODE BEGIN Private defines */

extern sgpio SGPIO_CODEC_RST;

/* USER CODE END Private defines */

#ifdef __cplusplus
}
#endif

#endif /* __MAIN_H */

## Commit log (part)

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2025-11-13 Initial
2025-11-15 schematics
2025-11-21 PCM3060 basic interface
2025-11-24 switch to SPI interface instead of I2C for PCM3060
2025-11-27 back to I2C for the read functionality, still cannot get it working
2025-12-02 ima errore PCM3060 -> STM32 ADC & CS4335 (PS2)
2025-12-03 PCB design, implement basic DAC/ADC
2025-12-04 PCB is done
2025-12-05 PCB prototype finishing touches
2025-12-19 izbrisi svg pdfove, zamjeni polaritet 2 diode
2026-03-26 ST7920, CS4271, new project direction
2026-04-04 Updated buttons and switched to I2S for the codec.
2026-04-04 KiCad 10
2026-04-05 Switched to new naming convention (MODULE_FunctionName, MODULE_VariableName etc.) Basic full-duplex I2S interface and CS4271 communication I2S full-duplex double buffering and mangling/unmangling
2026-04-05 Started work on the PCB. Started drawing the codec/STM32 part of the layout.
2026-04-06 PCB almost done.
2026-04-11 PCB done. Code, PCB screw holes and 3D design left
2026-04-11 Prints and renders.
2026-04-15 PCB work.
2026-06-27 Initial H7
